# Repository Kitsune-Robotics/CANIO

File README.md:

# CANIO

This repo contains all the firmware and hardware for the CANIO.

If you're looking for the latest docs/builds, see our [Releases Page](https://github.com/Kitsune-Robotics/CANIO/releases).

# Getting Started

First, clone this repo (and optionally checkout a branch)

```shell
git clone https://github.com/Kitsune-Robotics/CANIO.git
cd CANIO
```

# Init Submodules

Some libraries and resources are included as submodules, run the following
command to initialize them before opening the main sch

(If you get a missing library error, make sure to do this)

```shell
git submodule update --init --recursive
```

## Project Layout

If you want to use this project template for yourself, you can find it [here!](https://github.com/KenwoodFox/Project-Template)

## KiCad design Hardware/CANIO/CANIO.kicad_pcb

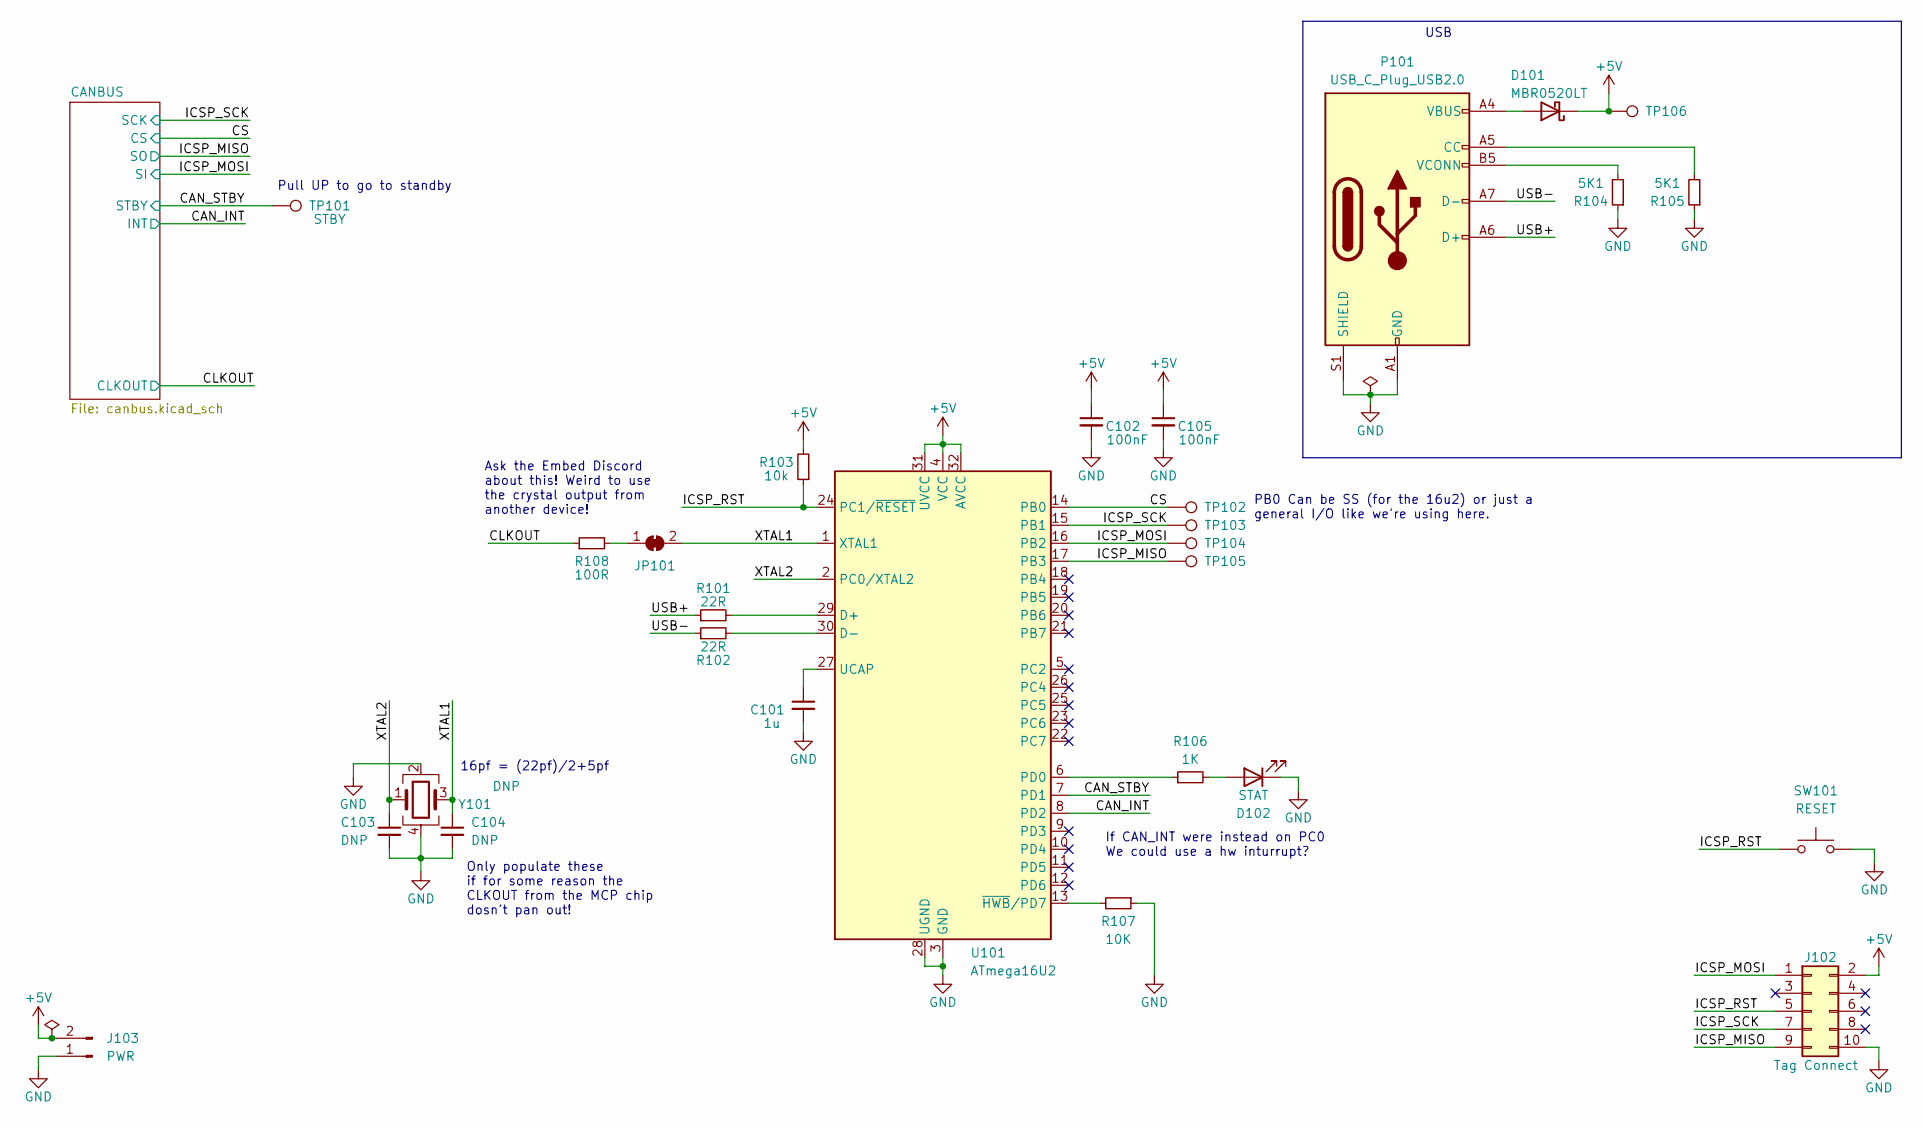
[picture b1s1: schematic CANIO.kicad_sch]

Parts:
C101: 1u; C_0805_2012Metric
C102, C105: 100nF; C_0805_2012Metric
C103, C104: DNP; C_0603_1608Metric
D101: MBR0520LT; D_SOD-123; LCSC# C165467
D102: STAT; LED_0805_2012Metric
J102: Tag Connect; Tag-Connect_TC2050-IDC-FP_2x05_P1.27mm_Vertical
J103: PWR; JST_XH_S2B-XH-A_1x02_P2.50mm_Horizontal
JP101: SolderJumper_2_Bridged; SolderJumper-2_P1.3mm_Bridged2Bar_Pad1.0x1.5mm
P101: USB_C_Plug_USB2.0; USB_C_Receptacle_XKB_U262-16XN-4BVC11_Full_Pads; LCSC# C2765186
R101, R102: 22R; R_0805_2012Metric
R103: 10k; R_0805_2012Metric
R104, R105: 5K1; R_0805_2012Metric; LCSC# C269748
R106: 1K; R_0805_2012Metric
R107: 10K; R_0805_2012Metric; LCSC# C269748
R108: 100R; R_0805_2012Metric
SW101: RESET; SW_PUSH_6mm_H4.3mm
TP101: STBY; TestPoint_Pad_2.0x2.0mm
TP102, TP103, TP104, TP105, TP106: TestPoint; TestPoint_Pad_2.0x2.0mm
U101: ATmega16U2; TQFP-32_7x7mm_P0.8mm; LCSC# C59019
Y101: DNP; Crystal_SMD_3225-4Pin_3.2x2.5mm; LCSC# C13738

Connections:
+5V: C102.1, C105.1, D101.1 (K), J102.2, J103.2, R103.2, TP106.1, U101.4 (VCC), U101.31 (UVCC), U101.32 (AVCC); also elsewhere on the board
/CAN_INT: U101.8 (PD2); also elsewhere on the board
/CAN_STBY: TP101.1, U101.7 (PD1); also elsewhere on the board
/CLKOUT: R108.1; also elsewhere on the board
/CS: TP102.1, U101.14 (PB0); also elsewhere on the board
/ICSP_MISO: J102.9, TP105.1, U101.17 (PB3); also elsewhere on the board
/ICSP_MOSI: J102.1, TP104.1, U101.16 (PB2); also elsewhere on the board
/ICSP_RST: J102.5, R103.1, SW101.1, U101.24 (PC1/~RESET)
/ICSP_SCK: J102.7, TP103.1, U101.15 (PB1); also elsewhere on the board
/USB+: P101.A6 (D+), R101.1
/USB-: P101.A7 (D-), R102.1
/XTAL1: C104.1, JP101.2 (B), U101.1 (XTAL1), Y101.3
/XTAL2: C103.1, U101.2 (PC0/XTAL2), Y101.1
GND: C101.2, C102.2, C103.2, C104.2, C105.2, D102.1 (K), J102.10, J103.1, P101.A1 (GND), P101.A12 (GND), P101.B1 (GND), P101.B12 (GND), P101.S1 (SHIELD), R104.1, R105.1, R107.1, SW101.2, U101.3 (GND), U101.28 (UGND), Y101.2, Y101.4; also elsewhere on the board
unnamed: D101.2 (A), P101.A4 (VBUS), P101.A9 (VBUS), P101.B4 (VBUS), P101.B9 (VBUS)
unnamed: D102.2 (A), R106.2
unnamed: JP101.1 (A), R108.2
unnamed: P101.A5 (CC), R105.2
unnamed: P101.B5 (VCONN), R104.2
unnamed: R101.2, U101.29 (D+)
unnamed: R102.2, U101.30 (D-)
unnamed: R106.1, U101.6 (PD0)
unnamed: C101.1, U101.27 (UCAP)
unnamed: R107.2, U101.13 (~HWB/PD7)

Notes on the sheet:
If CAN_INT were instead on PC0 We could use a hw inturrupt?
Ask the Embed Discord about this! Weird to use the crystal output from another device!
Pull UP to go to standby
Only populate these if for some reason the CLKOUT from the MCP chip dosn't pan out!
USB
PB0 Can be SS (for the 16u2) or just a general I/O like we're using here.
16pf = (22pf)/2+5pf

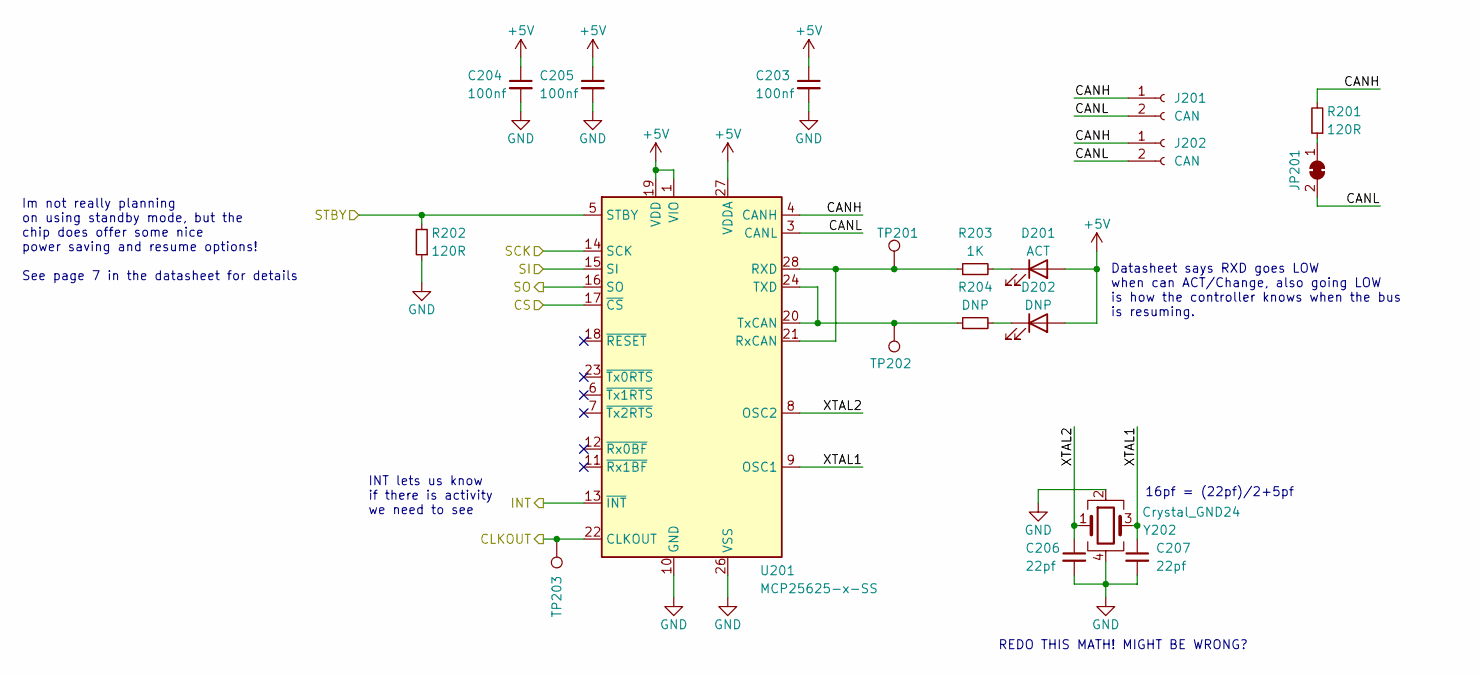
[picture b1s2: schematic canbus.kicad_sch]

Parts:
C203, C204, C205: 100nf; C_0805_2012Metric
C206, C207: 22pf; C_0603_1608Metric
D201: ACT; LED_0805_2012Metric
D202: DNP; LED_0805_2012Metric
J201, J202: CAN; SolderWire-0.5sqmm_1x02_P4.8mm_D0.9mm_OD2.3mm_Relief
JP201: TERM; SolderJumper-2_P1.3mm_Bridged2Bar_Pad1.0x1.5mm
R201: 120R; R_Axial_DIN0207_L6.3mm_D2.5mm_P10.16mm_Horizontal
R202: 120R; R_0805_2012Metric
R203: 1K; R_0805_2012Metric
R204: DNP; R_0805_2012Metric
TP201, TP202, TP203: TestPoint; TestPoint_Pad_2.0x2.0mm
U201: MCP25625-x-SS; SSOP-28_5.3x10.2mm_P0.65mm; LCSC# C628816
Y202: Crystal_GND24; Crystal_SMD_3225-4Pin_3.2x2.5mm; LCSC# C13738

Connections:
+5V: C203.1, C204.1, C205.1, D201.2 (A), D202.2 (A), U201.1 (VIO), U201.19 (VDD), U201.27 (VDDA); also elsewhere on the board
/CANBUS/CANH: J201.1, J202.1, R201.2, U201.4 (CANH)
/CANBUS/CANL: J201.2, J202.2, JP201.2 (B), U201.3 (CANL)
/CANBUS/XTAL1: C207.1, U201.9 (OSC1), Y202.3
/CANBUS/XTAL2: C206.1, U201.8 (OSC2), Y202.1
/CAN_INT: U201.13 (~INT); also elsewhere on the board
/CAN_STBY: R202.2, U201.5 (STBY); also elsewhere on the board
/CLKOUT: TP203.1, U201.22 (CLKOUT); also elsewhere on the board
/CS: U201.17 (~CS); also elsewhere on the board
/ICSP_MISO: U201.16 (SO); also elsewhere on the board
/ICSP_MOSI: U201.15 (SI); also elsewhere on the board
/ICSP_SCK: U201.14 (SCK); also elsewhere on the board
GND: C203.2, C204.2, C205.2, C206.2, C207.2, R202.1, U201.10 (GND), U201.26 (VSS), Y202.2, Y202.4; also elsewhere on the board
unnamed: D201.1 (K), R203.2
unnamed: D202.1 (K), R204.2
unnamed: JP201.1 (A), R201.1
unnamed: R203.1, TP201.1, U201.21 (RxCAN), U201.28 (RXD)
unnamed: R204.1, TP202.1, U201.20 (TxCAN), U201.24 (TXD)

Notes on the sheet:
INT lets us know if there is activity we need to see
REDO THIS MATH! MIGHT BE WRONG?
Datasheet says RXD goes LOW when can ACT/Change, also going LOW is how the controller knows when the bus is resuming.
16pf = (22pf)/2+5pf
Im not really planning on using standby mode, but the chip does offer some nice power saving and resume options! See page 7 in the datasheet for details

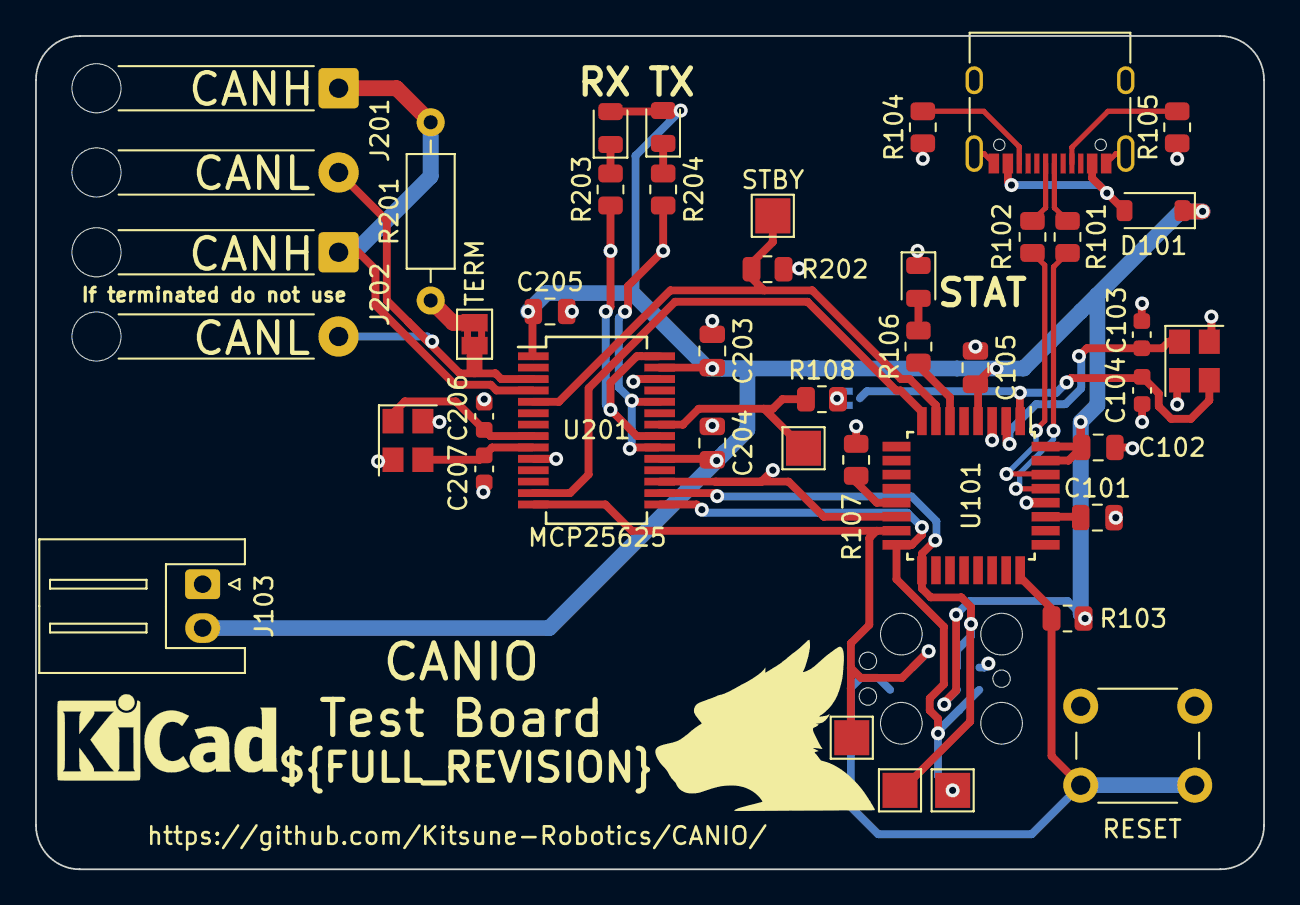
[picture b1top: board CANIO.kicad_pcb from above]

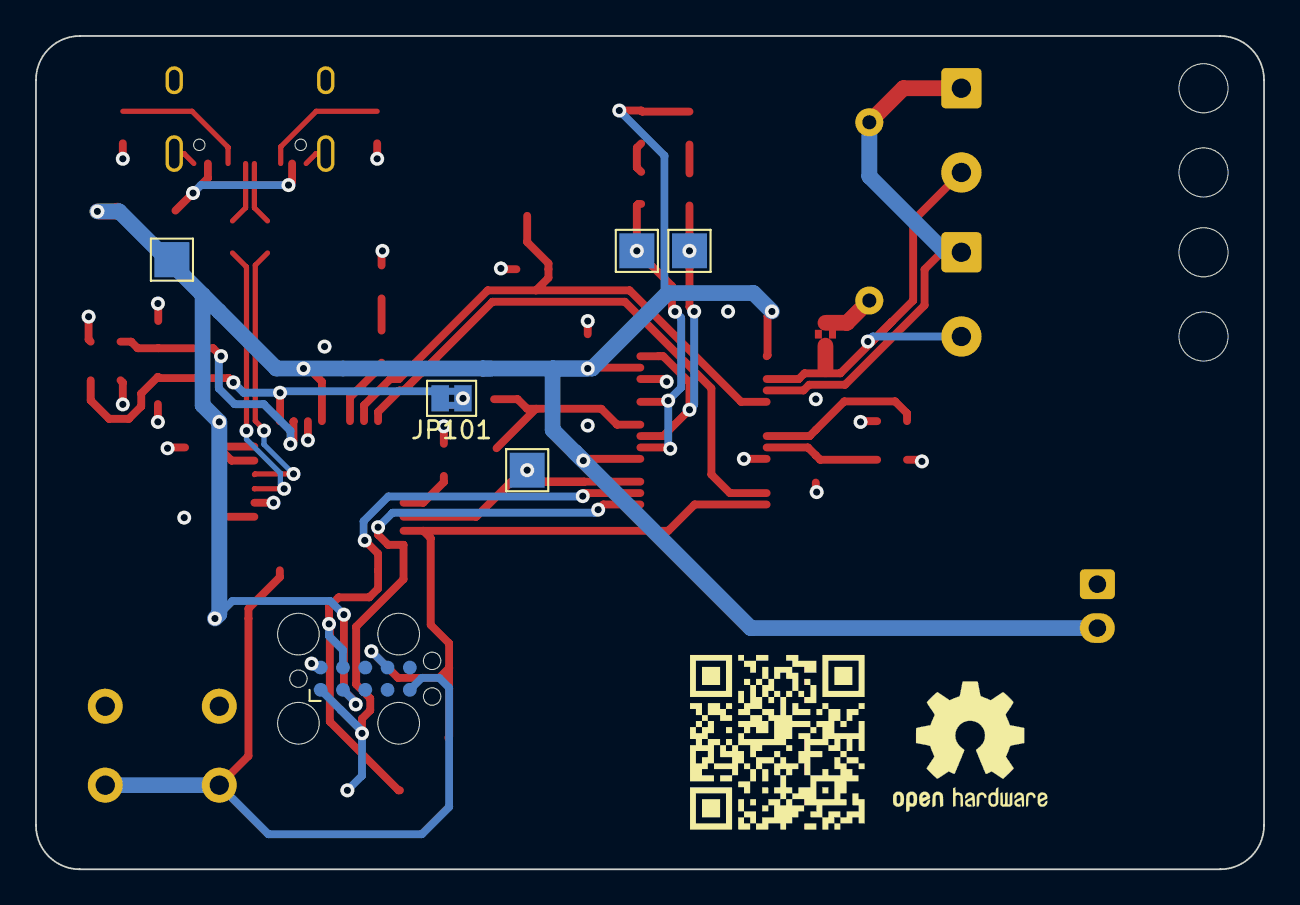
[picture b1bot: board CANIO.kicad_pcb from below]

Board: 4 copper layers, 70.0 x 47.5 mm, 47 parts (6 on the bottom side), 33 nets.

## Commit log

2024-01-10 Template from https://github.com/KenwoodFox/Project-Template
2024-01-10 Fix names
2024-01-10 Add kenwoodfox libs
2024-01-10 Add more boilerplate
2024-01-10 Add processor
2024-01-12 Bump
2024-01-12 Edge cuts and stuff
2024-01-12 Fix ERC
2024-01-12 Add 3d and discord
2024-01-12 Arthur is encouraging
2024-01-12 Always have a backup
2024-01-12 My favorite switch
2024-01-12 Design improvements, multilayer and more
2024-01-12 Do some routing
2024-01-12 Everything seems ship shape
2024-01-12 Add revision to silkscreen
2024-01-12 Add a few more comments
2024-01-13 include input from @ka2qfx
2024-01-17 Add term solder jumper
